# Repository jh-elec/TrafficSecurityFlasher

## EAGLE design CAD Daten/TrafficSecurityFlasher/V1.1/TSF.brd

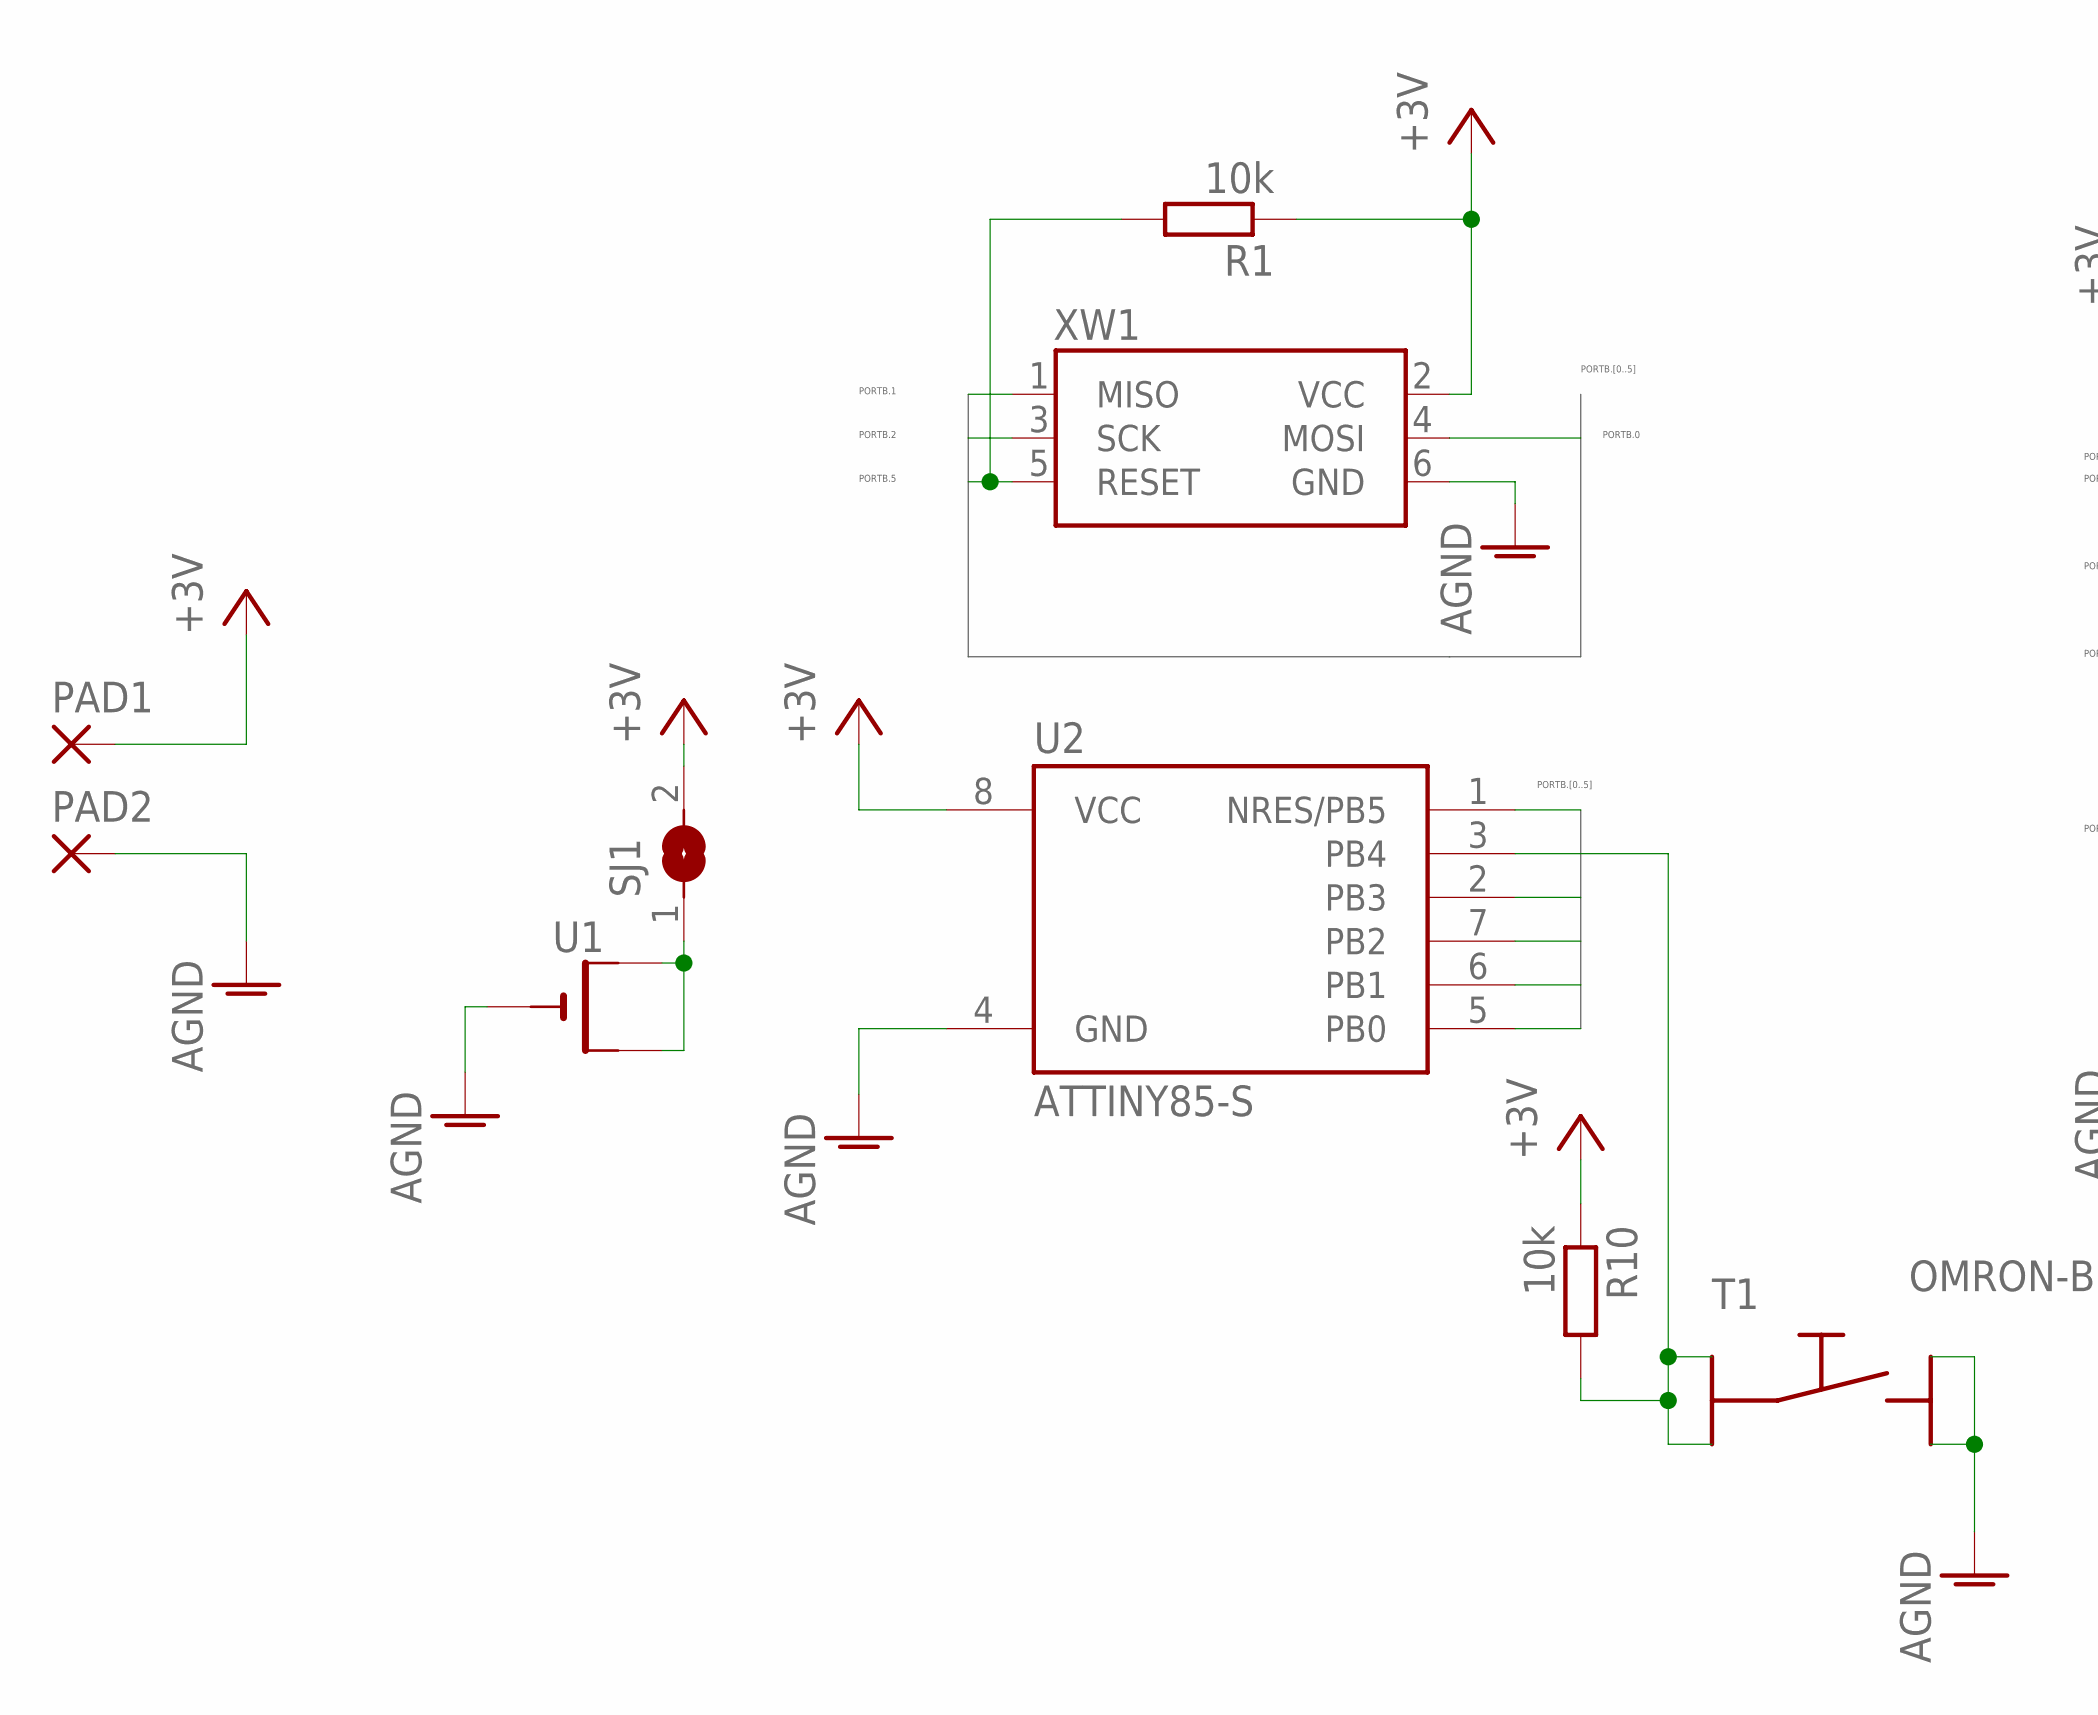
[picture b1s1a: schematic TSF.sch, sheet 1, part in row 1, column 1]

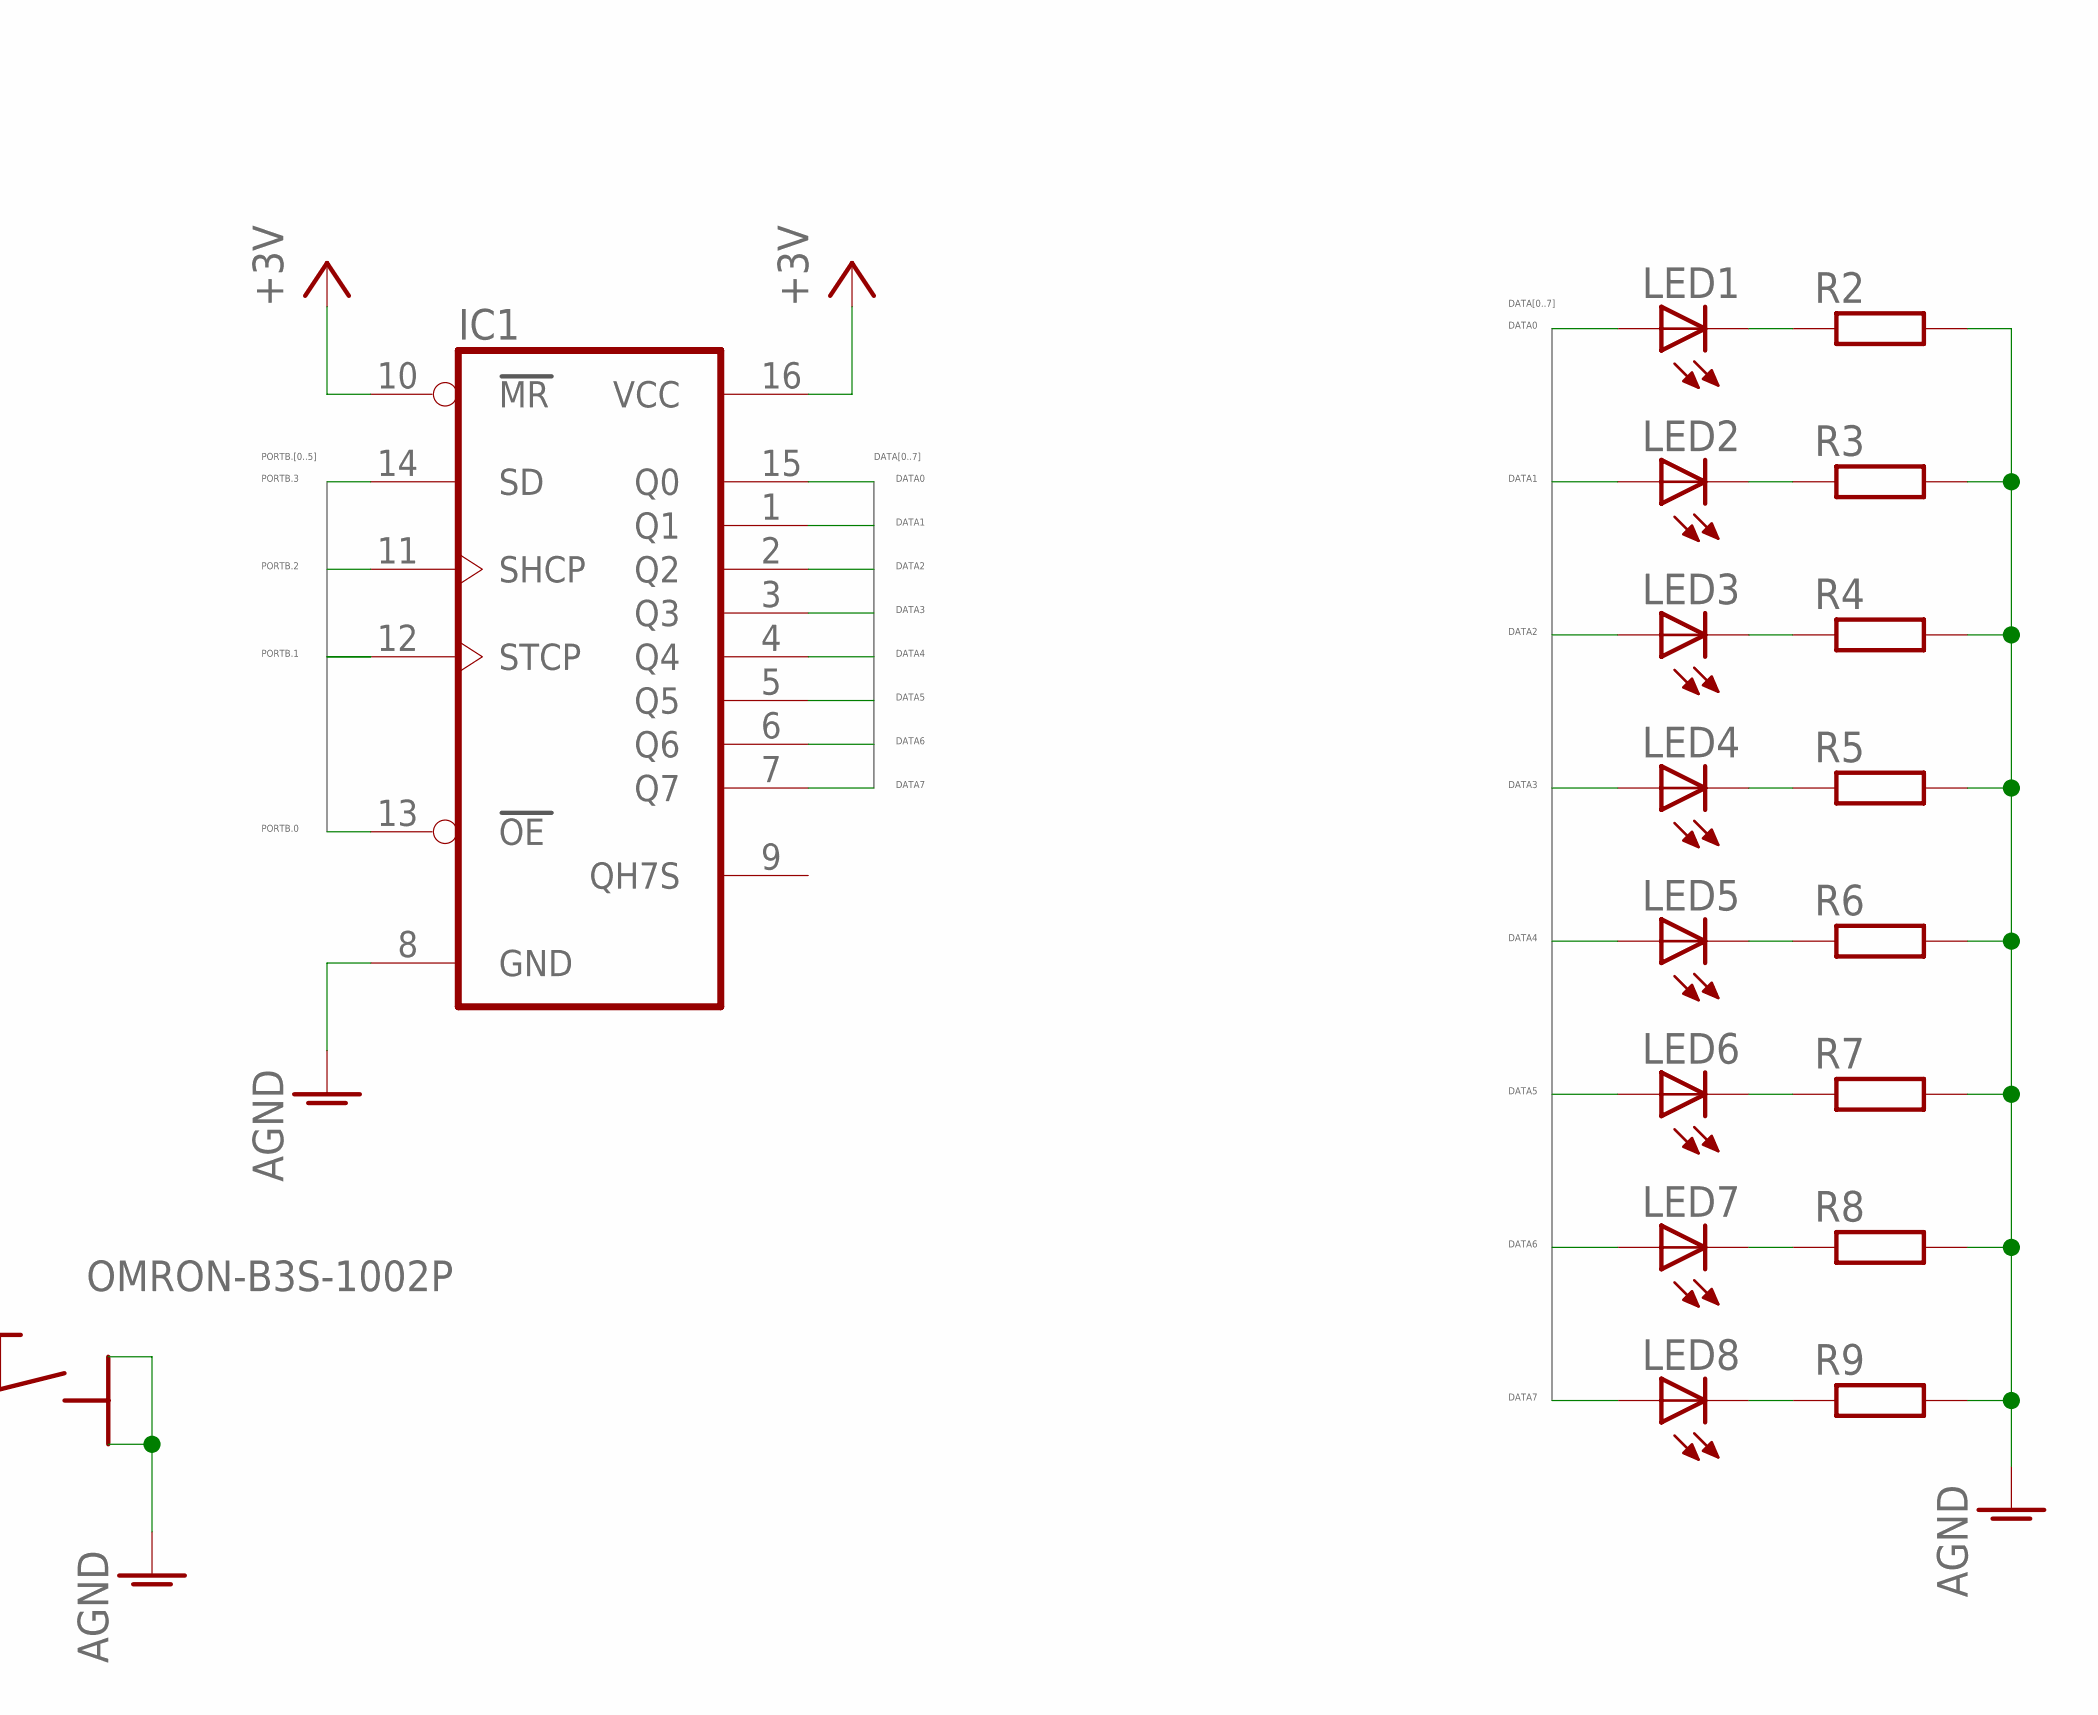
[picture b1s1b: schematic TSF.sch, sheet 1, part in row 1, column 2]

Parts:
IC1: 74HC595D; SO16
LED1, LED2, LED3, LED4, LED5, LED6, LED7, LED8: LEDP-LCC-2; P-LCC-2
PAD1, PAD2: SMD2; SMD1,27-2,54
R1, R10: 10k; R1206
R2, R3, R4, R5, R6, R7, R8, R9: R-EU_M1206; M1206
SJ1: SJW
T1: OMRON-B3S-1002P; B3S-1002P
U1: CR2032SMT; CR2032-SMD
U2: ATTINY85-S; SOIC8_EIAJ_208MIL
XW1: WSLSMD; WSL_SMD

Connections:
AGND: IC1.8 (GND), PAD2.1, R2.2, R3.2, R4.2, R5.2, R6.2, R7.2, R8.2, R9.2, T1.3, T1.4, U1.-, U2.4 (GND), XW1.6 (GND)
DATA0: IC1.15 (Q0), LED1.A
DATA1: IC1.1 (Q1), LED2.A
DATA2: IC1.2 (Q2), LED3.A
DATA3: IC1.3 (Q3), LED4.A
DATA4: IC1.4 (Q4), LED5.A
DATA5: IC1.5 (Q5), LED6.A
DATA6: IC1.6 (Q6), LED7.A
DATA7: IC1.7 (Q7), LED8.A
unnamed: SJ1.1, U1.+$1 (+), U1.+$2 (+1)
unnamed: LED1.C, R2.1
unnamed: LED2.C, R3.1
unnamed: LED3.C, R4.1
unnamed: LED4.C, R5.1
unnamed: LED5.C, R6.1
unnamed: LED6.C, R7.1
unnamed: LED7.C, R8.1
unnamed: LED8.C, R9.1
PORTB.0: IC1.13 (OE), U2.5 (PB0), XW1.4 (MOSI)
PORTB.1: IC1.12 (STCP), U2.6 (PB1), XW1.1 (MISO)
PORTB.2: IC1.11 (SHCP), U2.7 (PB2), XW1.3 (SCK)
PORTB.3: IC1.14 (SD), U2.2 (PB3)
PORTB.4: R10.2, T1.1, T1.2, U2.3 (PB4)
PORTB.5: R1.2, U2.1 (NRES/PB5), XW1.5 (RESET)
VCC: IC1.10 (MR), IC1.16 (VCC), PAD1.1, R1.1, R10.1, SJ1.2, U2.8 (VCC), XW1.2 (VCC)

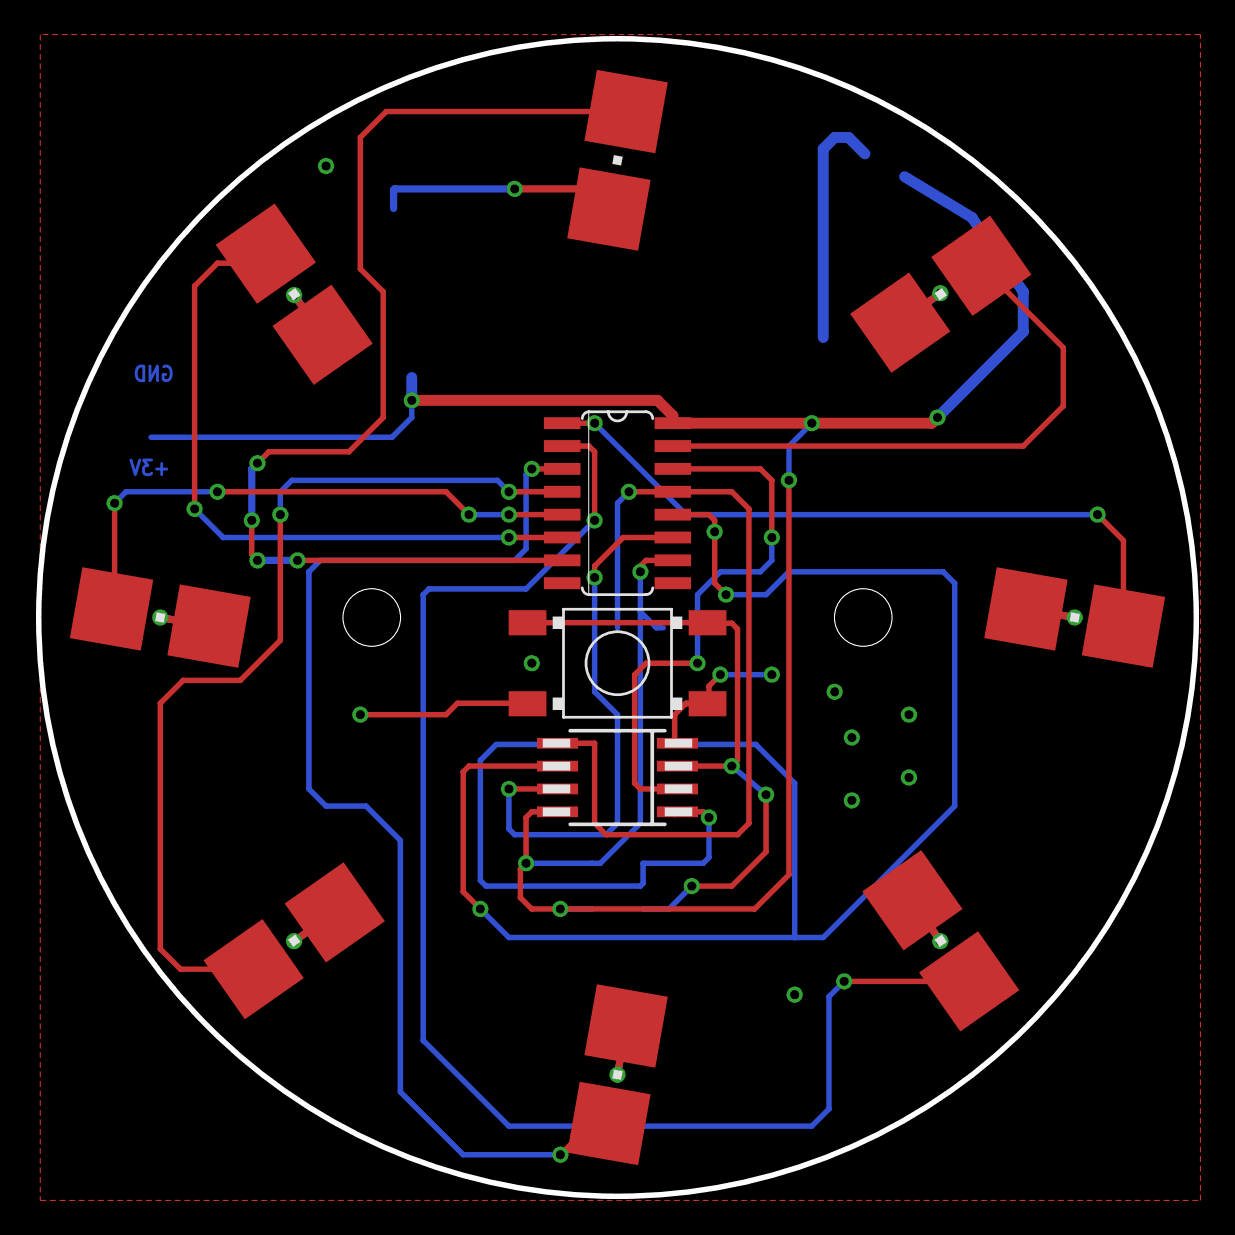
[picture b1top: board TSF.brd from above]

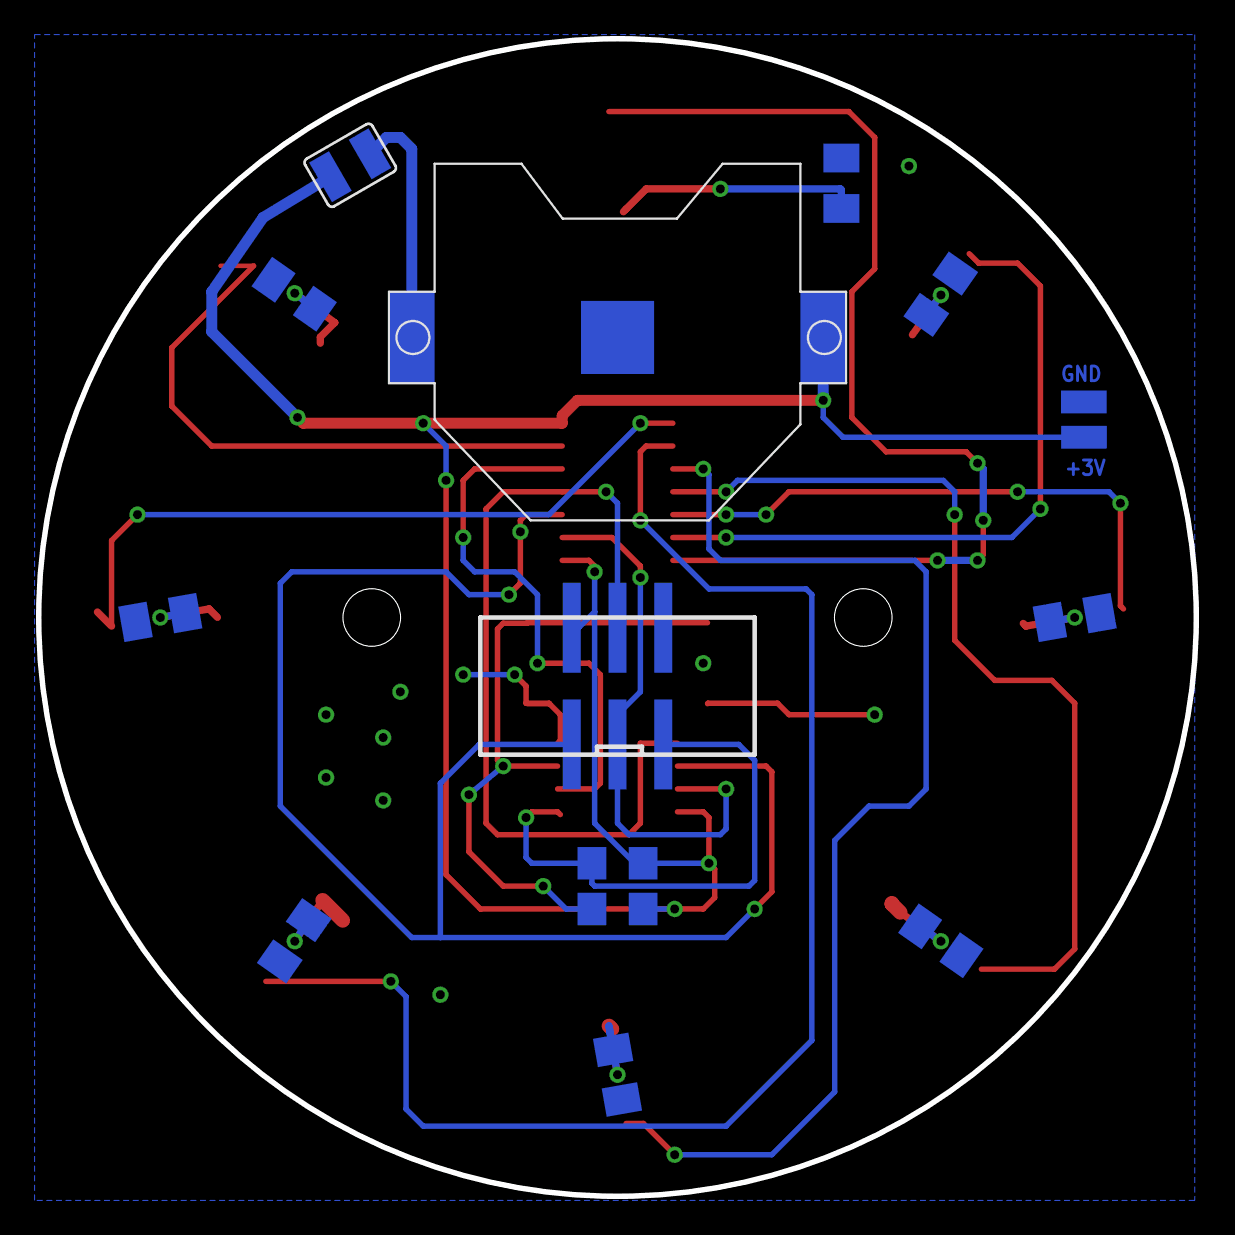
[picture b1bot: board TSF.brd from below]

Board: 2 copper layers, 64.3 x 64.3 mm, 27 parts (15 on the bottom side), 25 nets.

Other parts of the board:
U$1: 25X25_BEST

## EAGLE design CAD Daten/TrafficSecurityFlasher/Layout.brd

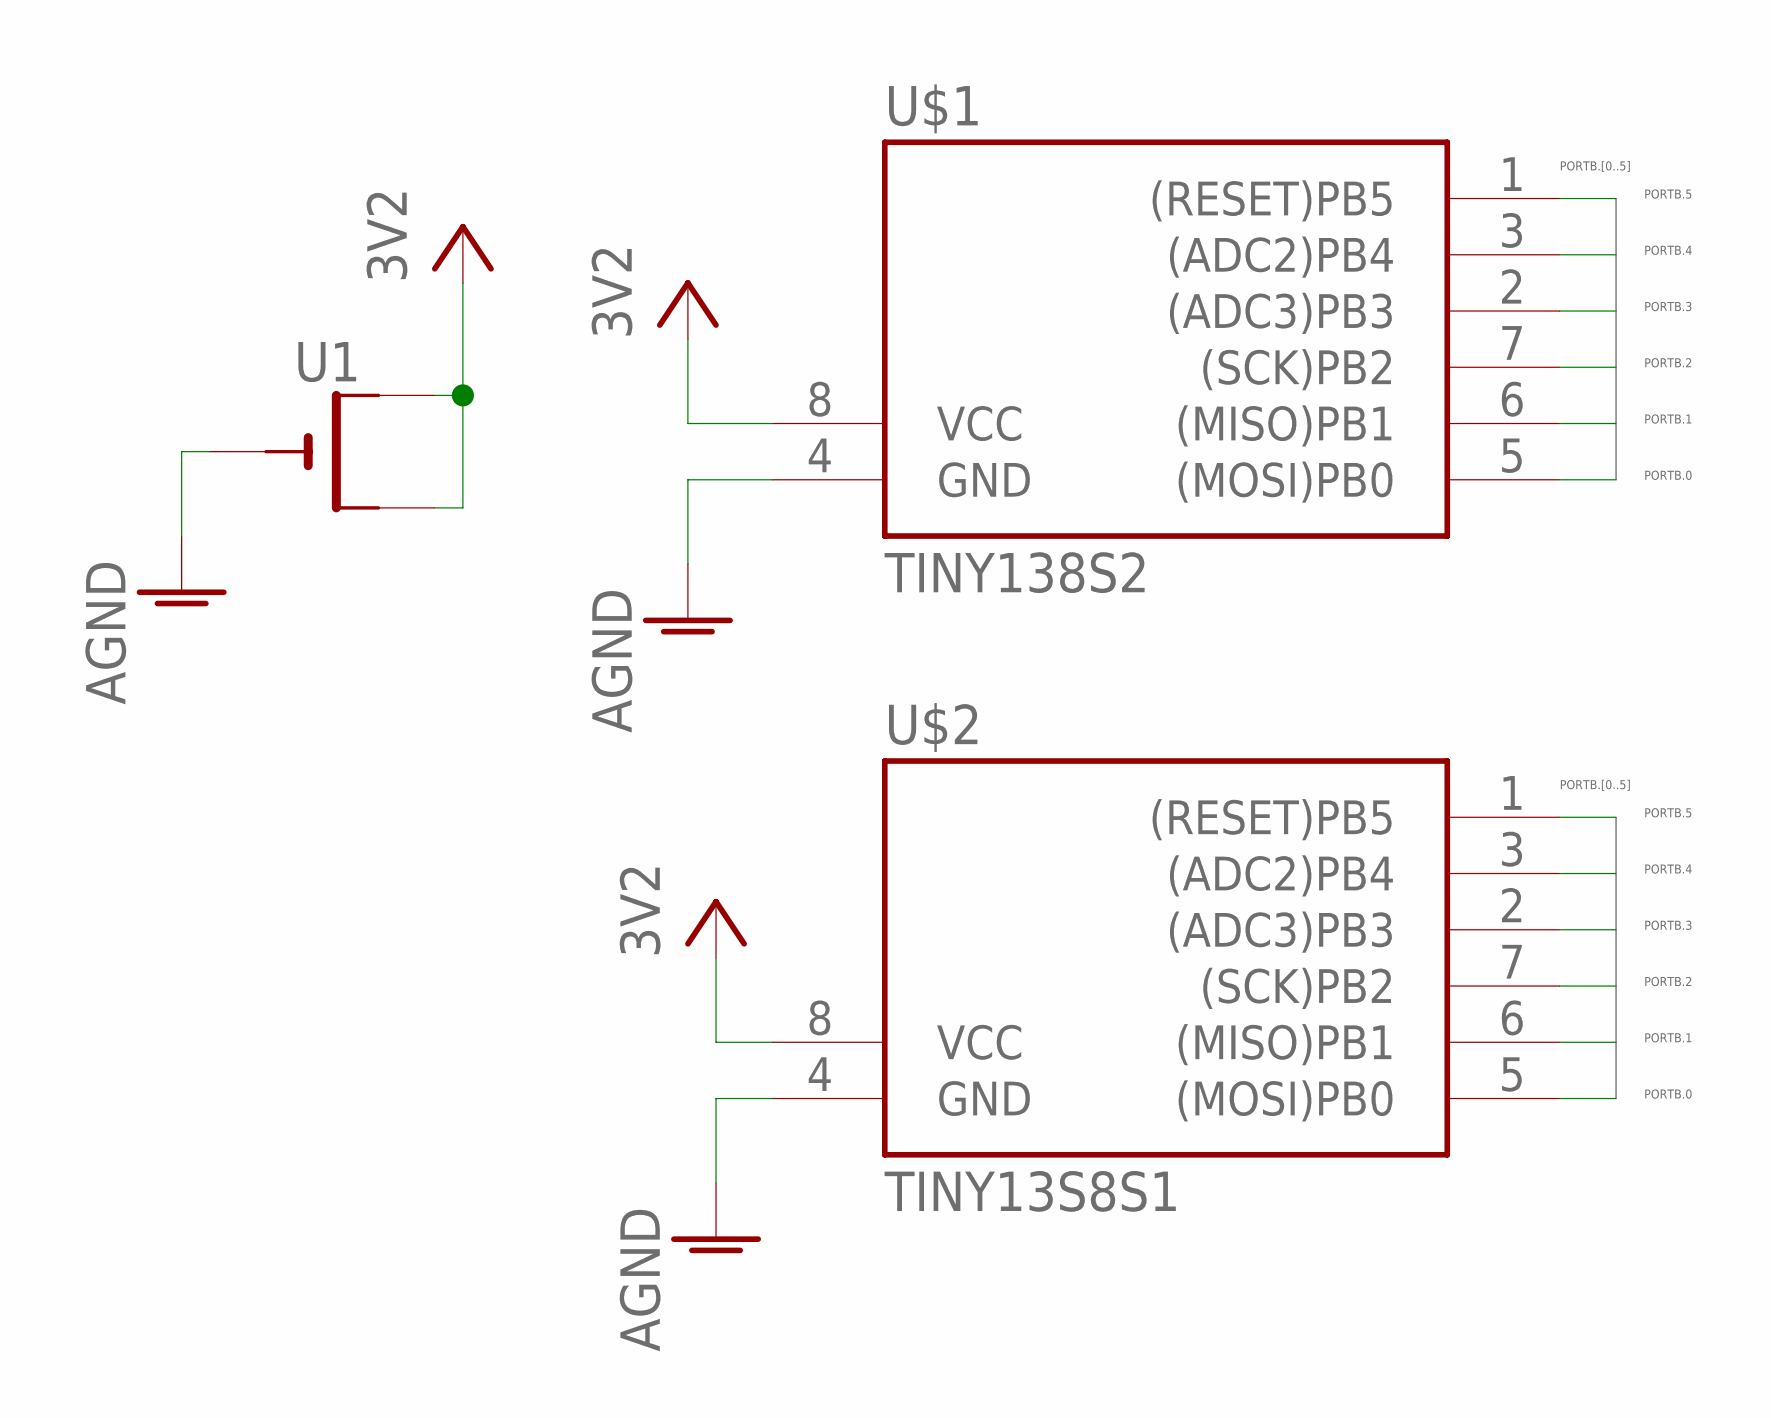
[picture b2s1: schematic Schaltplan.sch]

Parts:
U1: CR2032SMT; CR2032-SMD
U$1: TINY138S2; SO08
U$2: TINY13S8S1; SO08-GW

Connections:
AGND: U1.-, U$1.4 (GND), U$2.4 (GND)
PORTB.0: U$1.5 ((MOSI)PB0), U$2.5 ((MOSI)PB0)
PORTB.1: U$1.6 ((MISO)PB1), U$2.6 ((MISO)PB1)
PORTB.2: U$1.7 ((SCK)PB2), U$2.7 ((SCK)PB2)
PORTB.3: U$1.2 ((ADC3)PB3), U$2.2 ((ADC3)PB3)
PORTB.4: U$1.3 ((ADC2)PB4), U$2.3 ((ADC2)PB4)
PORTB.5: U$1.1 ((RESET)PB5), U$2.1 ((RESET)PB5)
VCC: U1.+$1 (+), U1.+$2 (+1), U$1.8 (VCC), U$2.8 (VCC)

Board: 2 copper layers, 3 parts (1 on the bottom side), 8 nets, no tracks yet.
